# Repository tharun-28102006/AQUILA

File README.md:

# FPGA-Based Environment-Adaptive Sonar Transmitter for AUVs

**This project presents an engineering prototype for environment-adaptive sonar transmission using an FPGA.** It contains Python reference models, SystemVerilog RTL and testbenches, an analog transmitter design, a KiCad PCB layout, and a CadQuery-generated mechanical payload model. It is not a completed or field-qualified sonar product.

The repository mixes runnable models and design artifacts. Physical performance, underwater operation, and hardware integration remain to be demonstrated.

**Prototype capabilities:** 81-state table-based profile selection, three waveform modes, ping-boundary profile control, Python/RTL simulation, and companion analog, PCB, and mechanical design artifacts.

## Quick Start

1. Clone and install the Python dependencies:

   ```powershell
   git clone https://github.com/tharun-28102006/AQUILA.git
   cd AQUILA
   python -m venv .venv
   .\.venv\Scripts\Activate.ps1
   python -m pip install --upgrade pip
   python -m pip install -r requirements.txt
   ```

   On Linux/macOS, use `python3 -m venv .venv` and `source .venv/bin/activate`.
2. Run `python python_model/system_simulation.py`. Plots and summary CSVs are written to `python_model/results/`.
3. Install Icarus Verilog and run the [RTL system test](#running-the-systemverilog-rtl-simulation). It writes `build/aquila_5msps.vcd`.
4. Browse the [simulation results](#simulation-results), [KiCad board](Aquila_pcb/AQUILA_TX_PCB_FIXED.kicad_pcb), [LTspice design](AQUILA_LTSPICE/), and [mechanical drawing](aquila-freecad/AQUILA_drawing.svg).

## System Architecture

```mermaid
flowchart TD
    ENV[Environmental inputs<br/>temperature, salinity, turbidity, range/depth] --> CLS[LOW / MEDIUM / HIGH classification]
    CLS --> ENC[4 x 2-bit state encoding<br/>8-bit address]
    ENC --> LUT[81-state adaptive LUT]
    LUT --> PROF[Frequency, bandwidth, pulse duration,<br/>amplitude, waveform mode]
    PROF --> LATCH[Ping profile latch<br/>update at ping boundary]
    LATCH --> WAVE{Waveform engine}
    WAVE --> LFM[LFM chirp]
    WAVE --> GEO[Geometric sweep]
    WAVE --> PHASE[Phase-coded pulse]
    LFM --> WIN[Digital windowing]
    GEO --> WIN
    PHASE --> WIN
    WIN --> DAC[DAC interface]
    DAC --> FILTER[Analog filter]
    FILTER --> DRIVER[Output driver]
    DRIVER --> OUT[Analog output / future transducer integration]
```

This is the intended signal path represented across models and designs. Physical sensor acquisition, sustained DAC streaming, analog measurements, and transducer integration are not established by these artifacts.

### Simulation Preview

This checked-in plot is a 4 ms, 300 kHz-center LFM example from the Python model, not a measured hardware waveform. Detailed [waveforms, FFTs, spectrograms, and provenance](#simulation-results) follow below.

## Project Overview

The proposed system selects a sonar pulse profile from four environmental inputs rather than using a single fixed profile. Temperature, salinity, turbidity, and AUV-to-seabed range/depth are classified into three discrete states. The selected profile is held stable during a ping and may be replaced at the next ping boundary.

### Problem and Proposed Solution

Water conditions and operating range can change during an AUV mission. The prototype investigates deterministic profile selection and FPGA waveform generation as a reconfigurable transmitter architecture. It encodes classified inputs, looks up a precomputed profile, validates it, and latches it for the ping. The lookup avoids computing a new profile through complex runtime propagation arithmetic. Thresholds and profile policy are assumptions, not experimentally calibrated environmental or propagation data.

## How the System Works

1. Python or RTL receives numeric environmental inputs. Physical sensors and acquisition electronics are not demonstrated here.
2. The classifier maps each input to LOW, MEDIUM, or HIGH.
3. The state encoder concatenates four 2-bit states into an 8-bit LUT address.
4. The LUT supplies center frequency, bandwidth, pulse duration, amplitude, and waveform mode.
5. A safety validator checks the requested profile. The ping-profile latch captures the first valid profile and updates it only after `ping_done`.
6. The selected waveform engine generates samples. The digital path includes windowing and a DAC sample interface.
7. Python behavioral analog models and a separate LTspice design represent the filter/output chain. Physical output and acoustic stages require future validation.

### Environmental-State Classification

These are prototype thresholds, not sensor calibration specifications. Salinity and turbidity units are not defined in the model documentation.

| Input | LOW | MEDIUM | HIGH |
|---|---|---|---|
| Temperature | below 20 C | 20-30 C, inclusive | above 30 C |
| Salinity | below 300 | 300-600, inclusive | above 600 |
| Turbidity | below 20 | 20-100, inclusive | above 100 |
| Range/depth | below 1 m | 1-3 m, inclusive | above 3 m |

Python code: [`classifier.py`](python_model/classifier.py), [`environment.py`](python_model/environment.py), [`config.py`](python_model/config.py). RTL logic: [`sensor_classifier.sv`](rtl/sensor_classifier.sv). LOW, MEDIUM, and HIGH encode as `00`, `01`, and `10`; `11` is unused.

### 81-State Adaptive LUT

There are four inputs, each with three valid classes, so there are 3 x 3 x 3 x 3 = 81 valid combinations. Each class uses 2 bits; temperature, salinity, turbidity, and range/depth are concatenated in that order to form the 8-bit address. The other address patterns are not valid classifier outputs.

[`python_model/adaptive_lut.py`](python_model/adaptive_lut.py) builds and checks the reference table. RTL/Python generated tables are [`rtl/adaptive_lut.sv`](rtl/adaptive_lut.sv) and [`python_model/adaptive_lut.sv`](python_model/adaptive_lut.sv); reference data is [`python_model/adaptive_lut_reference.csv`](python_model/adaptive_lut_reference.csv). The current policy starts from a range-state profile, adjusts frequency for temperature/salinity and bandwidth for turbidity, then checks configured limits. It is a deterministic prototype policy, not a propagation-trained or experimentally calibrated LUT.

The main Python simulation selects these demonstration profiles:

| Case | Address | Center frequency | Sweep | Duration | Amplitude control | Mode |
|---|---:|---:|---:|---:|---:|---|
| Geometric | `0x50` | 400 kHz | 360-440 kHz | 2 ms | 600/1000 | Geometric |
| LFM | `0x51` | 300 kHz | 260-340 kHz | 4 ms | 800/1000 | LFM |
| Phase-coded | `0x52` | 180 kHz | 150-210 kHz | 8 ms | 1000/1000 | Phase-coded |

Amplitude is a model control on a 0-1000 scale, not a physical DAC voltage.

### Waveform Generation

The active Python system waveform builder is `generate_waveform()` in [`python_model/system_simulation.py`](python_model/system_simulation.py). The standalone LFM helper is [`python_model/waveform_lfm.py`](python_model/waveform_lfm.py). RTL mode dispatch is in [`rtl/aquila_waveform_top.sv`](rtl/aquila_waveform_top.sv) and [`rtl/mode_selector.sv`](rtl/mode_selector.sv).

#### LFM Chirp

The Python system model increments instantaneous frequency from the profile sweep start toward its end over the pulse, then applies a Hann window for analysis. RTL uses [`rtl/lfm_waveform_generator.sv`](rtl/lfm_waveform_generator.sv), [`rtl/lfm_dds.sv`](rtl/lfm_dds.sv), and the sine LUT. These are generated electrical samples, not acoustic transmission.

#### Geometric Frequency Sweep

The Python system model uses geometrically spaced instantaneous frequencies (`numpy.geomspace`). RTL uses [`rtl/geometric_waveform_engine.sv`](rtl/geometric_waveform_engine.sv), selected through the mode selector. Its frequency progression is not linear like an LFM chirp.

#### Phase-Coded Pulse

The Python model applies discrete phase reversals to a carrier. RTL uses [`rtl/phase_coded_waveform_engine.sv`](rtl/phase_coded_waveform_engine.sv) and [`rtl/phase_code_lut.sv`](rtl/phase_code_lut.sv). The separate LTspice stimulus documents its own seven-chip illustrative sequence; do not assume the implementations are identical or that they implement a named Barker code.

### Ping-Boundary Parameter Control

[`rtl/ping_profile_latch.sv`](rtl/ping_profile_latch.sv) captures the first valid profile, then holds frequency, bandwidth, duration, amplitude, and mode until `ping_done`. The system test changes requested environmental inputs during a ping and checks that the active mode changes at the boundary. Python includes a corresponding assertion in `validate_ping_boundary()`. Neither test establishes physical sensor-to-DAC operation.

## Digital Simulation

The main Python entry point is [`python_model/system_simulation.py`](python_model/system_simulation.py). It checks the demonstration environment/address, all 81 LUT profiles, frequency limits, waveform/window generation, behavioral DAC/filter/output calculations, FFT/spectrogram analysis, ping-boundary behavior, and estimated DAC-interface rates.

The main SystemVerilog integration test is [`rtl/tb_aquila_system_5msps.sv`](rtl/tb_aquila_system_5msps.sv), with top-level system wiring in [`rtl/aquila_system_top.sv`](rtl/aquila_system_top.sv). Other benches cover LUT, classifier, waveform, timing, windowing, SPI, and stream-engine blocks. Some captures are standalone or legacy-rate experiments; the 5 MSPS system test is the documented current integration bench.

## Simulation Results

The following checked-in PNGs are Python reference/system-model outputs unless otherwise stated. They are generated waveforms and numerical analyses, not oscilloscope, hydrophone, or native LTspice measurements. Per-case metrics are in [`python_model/results/system_summary.csv`](python_model/results/system_summary.csv).

### LFM Waveform

This is the windowed 4 ms LFM example at LUT address `0x51` (300 kHz center, 80 kHz bandwidth) in the 5 MSPS Python model. It shows the modeled pulse envelope and sample waveform, not a measured DAC output. See [CSV metrics](python_model/results/system_summary.csv) and [generator](python_model/system_simulation.py).

### Geometric Sweep

| Time-domain output | Time-frequency view |
|---|---|
|  |  |

This is the 2 ms, 360-440 kHz example at address `0x50`. The spectrogram shows the modeled frequency progression during the pulse.

### Phase-Coded Pulse

| Time-domain output | FFT |
|---|---|
|  |  |

This is the 8 ms phase-coded example at address `0x52`, with a 180 kHz carrier profile and 60 kHz profile bandwidth. The FFT is computed from generated, windowed samples, not measured acoustic output.

### LFM Spectrum and Spectrogram

| FFT | Spectrogram |
|---|---|
|  |  |

The FFT shows frequency-domain content from the modeled pulse; the spectrogram shows frequency change over time. Both are regenerated by the Python system simulation.

### LUT Selection and Ping Update

The profile table above comes from the checked-in [`system_summary.csv`](python_model/results/system_summary.csv), which records each demonstration case's states, address, sweep, duration, mode, and modeled output metrics. The [5 MSPS RTL VCD](aquila_5msps.vcd) and [testbench](rtl/tb_aquila_system_5msps.sv) expose `lut_address`, `requested_fc`, `requested_mode`, `active_fc`, `active_mode`, `active_valid`, `profile_valid`, `ping_done`, `sample_enable`, `waveform_sample`, and `dac_sample`. The testbench reports initial/boundary profiles and asserts that active mode does not change before `ping_done`; it does not create a dedicated profile-transition plot.

### Analog Numerical Results

This response plot comes from the independent Python/SciPy analysis, not a native LTspice run. See its [validation summary](AQUILA_LTSPICE/results/validation_summary.json) and [CSV data](AQUILA_LTSPICE/results/ac_response/filter_response.csv) for provenance and values.

Other checked-in CSV captures, VCDs, FFTs, and spectrograms are under [`rtl/`](rtl/) and [`python_model/results/`](python_model/results/). `rtl/` includes standalone and legacy-rate artifacts; do not assume every capture came from the main system test.

## Analog Signal Chain

The repository contains two different analog representations:

- [`python_model/analog_validation.py`](python_model/analog_validation.py) implements a behavioral DAC quantizer, filter, and output/load calculations. Model values and power results are assumptions/estimates, not physical measurements.
- [`AQUILA_LTSPICE/`](AQUILA_LTSPICE/) contains schematics/models for a DAC equivalent, OPA2835 buffer, two Sallen-Key filter sections, OPA2684 current-feedback output-driver equivalent, and 50-ohm load. See its README and engineering report for model provenance and limitations.

The PCB design file places an AD3541R footprint, level translators, OPA2835 buffer/filter stages, OPA2684 driver, regulator, GPIO header, external-power terminal, SMA output, and test points. These related designs are not proof of an assembled electrical implementation.

## LTspice Design

Open [`AQUILA_LTSPICE/AQUILA_TX_ANALOG.asc`](AQUILA_LTSPICE/AQUILA_TX_ANALOG.asc) for the main schematic or [`AQUILA_LTSPICE/AQUILA_FILTER_DETAIL.asc`](AQUILA_LTSPICE/AQUILA_FILTER_DETAIL.asc) for the standalone filter. The equivalent main deck is [`AQUILA_LTSPICE/AQUILA_TX_ANALOG.cir`](AQUILA_LTSPICE/AQUILA_TX_ANALOG.cir). Keep local symbols/includes/models together. Full controls and test benches are in [`AQUILA_LTSPICE/README_AQUILA_LTSPICE.md`](AQUILA_LTSPICE/README_AQUILA_LTSPICE.md).

### Native LTspice Status

Native LTspice and alternate SPICE execution were **not performed** for the checked-in numerical results. The plots and CSVs are from an independent Python/SciPy linearized numerical method; the script does not run the SPICE decks or TI macromodel. Native schematic parsing, convergence, and vendor-model compatibility remain unverified. Do not cite these artifacts as native LTspice measurements.

### Running the Numerical Analog Validation

This runs the Python/SciPy validator, not LTspice. From the repository root:

```powershell
python -m pip install -r .\AQUILA_LTSPICE\scripts\requirements.txt
python .\AQUILA_LTSPICE\scripts\validate_numerically.py
```

It writes plots, CSVs, and JSON under `AQUILA_LTSPICE/results/`. [`AQUILA_LTSPICE/scripts/requirements.txt`](AQUILA_LTSPICE/scripts/requirements.txt) pins this tool's dependencies. [`build_project.py`](AQUILA_LTSPICE/scripts/build_project.py) regenerates design files from a manifest and can overwrite manual edits. To inspect the design, install LTspice separately and open the `.asc` file with its sibling symbols, includes, and models in place.

## PCB Design

The board source is [`Aquila_pcb/AQUILA_TX_PCB_FIXED.kicad_pcb`](Aquila_pcb/AQUILA_TX_PCB_FIXED.kicad_pcb), a KiCad 10-format board. There is no matching `.kicad_sch`, BOM, exported fabrication package, PCB render, or included DRC report. Board dimensions are not documented separately in the reports.

The placed design identifies an AD3541R DAC footprint, SN74AXC4T774 level translators, OPA2835 buffer/filter stages, OPA2684 output driver, AP2112K 1.8 V regulator, DE10-Lite GPIO header, external-power terminal, SMA output, and labeled test points/nets. The apparent signal path from the component/net labels is DE10-Lite GPIO header -> level translators -> DAC -> OPA2835 buffer -> two filter sections -> OPA2684 output driver -> SMA/output. This is an interpretation of the board file, not a verified signal-chain test; there is no matching schematic. These are design-file details, not evidence of DRC clearance, fabrication, assembly, or testing. Verify schematic correspondence, footprints, routing, clearances, and ratings before manufacturing. No KiCad CLI/rendering tool was available, so no board image or DRC result is claimed here.

## Mechanical CAD / Payload

The mechanical package describes a transmitter enclosure and payload layout, not a receiver/hydrophone assembly. Its nominal envelope is approximately 330 mm long x 138 mm wide x 129 mm high; the shell is 300 mm long, 110 mm outside diameter, and 102 mm inside diameter. The drawing is a general arrangement, not a released fabrication drawing.

- [Assembled named-part STEP](aquila-freecad/AQUILA_assembly.step)
- [Exploded STEP presentation model](aquila-freecad/AQUILA_exploded.step); exploded positions are not assembly positions
- [Individual STEP and STL parts](aquila-freecad/parts/)
- [Printable-parts ZIP](aquila-freecad/AQUILA_printable_parts.zip), containing 11 custom printable parts
- [Parametric CadQuery source](aquila-freecad/source/aquila.py)
- [Build notes](aquila-freecad/BUILD_NOTES.md) and [validation metadata](aquila-freecad/validation.json)

No native FreeCAD `.FCStd` file is included; the editable master is the CadQuery Python source. Recorded CAD checks cover B-rep validity and selected nominal fit/STEP round trips, not comprehensive tolerance, pressure, seal, thermal, fatigue, or certification analyses. The housing is **not pressure-rated or certified waterproof**. Some board/connector envelopes are placeholders pending measurement against actual parts.

## Complete Development Flow

```mermaid
flowchart LR
    A[Environmental model] --> B[State classifier and encoder]
    B --> C[Adaptive LUT]
    C --> D[Profile and ping latch]
    D --> E[SystemVerilog waveform RTL]
    E --> F[Python and RTL simulations]
    F --> G[Analog design and numerical analysis]
    G --> H[KiCad PCB design]
    H --> I[Mechanical integration model]
    I -. future .-> J[Bench electrical and thermal validation]
    J -. future .-> K[Water, tank, transducer testing]
    K -. future .-> L[AUV integration and field evaluation]
```

The code, simulations, analog/PCB designs, and CAD package are present. Dotted stages are future validation, not completed milestones.

## Repository Structure

| Path | Contents |
|---|---|
| [`python_model/`](python_model/) | Python models, simulations, LUT tools, analog/transducer studies, validators, results. |
| [`python_model/results/`](python_model/results/) | System summary and analog-response CSVs, waveform/FFT/spectrogram PNGs. |
| [`rtl/`](rtl/) | SystemVerilog modules/testbenches, capture-analysis scripts, CSVs, plots, and historical simulation artifacts. |
| [`Aquila_pcb/`](Aquila_pcb/) | KiCad PCB layout only; no matching schematic/BOM. |
| [`AQUILA_LTSPICE/`](AQUILA_LTSPICE/) | Schematics, decks, includes, symbols/models, numerical scripts and result files. |
| [`aquila-freecad/`](aquila-freecad/) | STEP/STL, CadQuery source, drawing, parameters, build notes, manifest, checksums, validation. |
| [`AQUILA_AUDIT_REPORT.md`](AQUILA_AUDIT_REPORT.md) | Architecture audit, interface rates, and outstanding hardware work. |
| [`requirements.txt`](requirements.txt) | Python dependencies for the main model/analysis scripts. |

The transducer-aware scripts and related files in `python_model/` are historical study artifacts, not the active final system path. Existing VCD, CSV, and PNG files are reference results; compiled simulator executables are not source.

## Requirements and Tools

| Area | Technology |
|---|---|
| FPGA target context | Intel MAX 10 / DE10-Lite appears in project interfaces/CAD notes; physical timing closure is not established. |
| HDL / RTL simulation | SystemVerilog; Icarus Verilog (`iverilog`, `vvp`); GTKWave optional for viewing VCD. |
| Python model | Python 3, NumPy, SciPy, Matplotlib; pandas is used by capture-analysis utilities. |
| Analog design | LTspice-compatible `.asc`/`.cir` sources and local models; native execution unverified. |
| Analog numerical analysis | Python/NumPy/SciPy/Matplotlib; pinned requirements in `AQUILA_LTSPICE/scripts/requirements.txt`. |
| PCB | KiCad 10-format board source. |
| Mechanical | CadQuery 2.5.2 source; STEP/STL viewable in FreeCAD or another compatible CAD tool. |
| Version control | Git / GitHub |

## Installation

### Python

Windows PowerShell:

```powershell
python -m venv .venv
.\.venv\Scripts\Activate.ps1
python -m pip install --upgrade pip
python -m pip install -r requirements.txt
```

Linux or macOS:

```bash
python3 -m venv .venv
source .venv/bin/activate
python -m pip install --upgrade pip
python -m pip install -r requirements.txt
```

If activation is blocked, invoke `.\.venv\Scripts\python.exe -m pip install -r requirements.txt` and use `.\.venv\Scripts\python.exe` to run the model.

### RTL Simulator

Install Icarus Verilog with SystemVerilog support and put `iverilog` and `vvp` on `PATH`. Install GTKWave separately if you want a VCD GUI. The compile/run commands below were verified with Icarus Verilog 12.0; this version prints some non-fatal `constant selects in always_*` warnings for the current RTL.

## Running the Python Model

From the repository root with the environment active:

```powershell
python python_model/system_simulation.py
```

This prints PASS checks and creates/updates `system_summary.csv`, `analog_response.csv`, and available mode-specific time, FFT, and spectrogram plots in `python_model/results/`. Analog-chain and power values are modeled estimates, not physical measurements.

Other scripts include [`waveform_lfm.py`](python_model/waveform_lfm.py), [`adaptive_lut.py`](python_model/adaptive_lut.py), [`analog_validation.py`](python_model/analog_validation.py), and [`fft_analysis.py`](python_model/fft_analysis.py). Some scripts are standalone or historical; inspect their assumptions before treating output as part of the main system validation.

## Running the SystemVerilog RTL Simulation

The integration test is `tb_aquila_system_5msps` in [`rtl/tb_aquila_system_5msps.sv`](rtl/tb_aquila_system_5msps.sv). It checks profile safety, ping-boundary changes, and sample-enable timing. Its 50 MHz clock and 5 MSPS internal sample-enable target correspond to 200 ns between events.

Windows PowerShell, from the repository root:

```powershell
New-Item -ItemType Directory -Force .\build | Out-Null
$rtl = Get-ChildItem .\rtl -Filter *.sv |
    ForEach-Object { $_.FullName }

iverilog -g2012 `
    -s tb_aquila_system_5msps `
    -o .\build\aquila_5msps.vvp `
    $rtl

if ($LASTEXITCODE -eq 0) {
    Push-Location .\build
    try {
        vvp .\aquila_5msps.vvp
    }
    finally {
        Pop-Location
    }
}
```

Linux/macOS, from the repository root:

```bash
mkdir -p build
iverilog -g2012 \
    -s tb_aquila_system_5msps \
    -o build/aquila_5msps.vvp \
    rtl/*.sv

(cd build && vvp ./aquila_5msps.vvp)
```

Expected success line: `PASS: Aquila 5-MSPS system-level RTL simulation`. The VCD is written to `build/aquila_5msps.vcd`, and `build/` is Git-ignored. The existing root `aquila_5msps.vcd` is a checked-in reference capture and is not overwritten by these commands.

## Viewing Waveform Results

Open the generated VCD from the repository root:

```powershell
gtkwave .\build\aquila_5msps.vcd
```

On Linux/macOS, use `gtkwave build/aquila_5msps.vcd`. Useful testbench signals are `temperature_state`, `salinity_state`, `turbidity_state`, `range_state`, `lut_address`, `requested_fc`, `requested_mode`, `active_fc`, `active_mode`, `active_valid`, `profile_valid`, `ping_done`, `sample_enable`, `waveform_sample`, and `dac_sample`. They are declared in the testbench and present in the VCD header. GTKWave is optional for running the test.

## Viewing the KiCad PCB

Open [`Aquila_pcb/AQUILA_TX_PCB_FIXED.kicad_pcb`](Aquila_pcb/AQUILA_TX_PCB_FIXED.kicad_pcb) in KiCad. Only the board file is present; there is no companion schematic, BOM, render, fabrication output, or DRC report. Verify the design and manufacturing constraints before use.

## Viewing LTspice and Running Numerical Validation

Open [`AQUILA_LTSPICE/AQUILA_TX_ANALOG.asc`](AQUILA_LTSPICE/AQUILA_TX_ANALOG.asc) in LTspice with sibling symbols, includes, and models in place. The standalone filter schematic is [`AQUILA_LTSPICE/AQUILA_FILTER_DETAIL.asc`](AQUILA_LTSPICE/AQUILA_FILTER_DETAIL.asc). See the [LTspice project guide](AQUILA_LTSPICE/README_AQUILA_LTSPICE.md) for test decks, control values, traces, and model provenance.

The checked-in result plots are from independent Python/SciPy linearized analysis, **not native LTspice**. Native LTspice and alternate SPICE execution were not performed for these results; native parsing, convergence, and vendor-model compatibility remain unverified.

To run the numerical analog validator from the repository root (this does not run LTspice):

```powershell
python -m pip install -r .\AQUILA_LTSPICE\scripts\requirements.txt
python .\AQUILA_LTSPICE\scripts\validate_numerically.py
```

It writes plots, CSVs, and a JSON summary under `AQUILA_LTSPICE/results/`. [`AQUILA_LTSPICE/scripts/requirements.txt`](AQUILA_LTSPICE/scripts/requirements.txt) pins the analysis dependencies. [`build_project.py`](AQUILA_LTSPICE/scripts/build_project.py) regenerates design files from a manifest and can overwrite manual edits.

## Mechanical CAD / Payload

This is a transmitter enclosure/payload layout, not a receiver/hydrophone assembly. The nominal envelope is about 330 x 138 x 129 mm; the shell is 300 mm long, 110 mm outside diameter, and 102 mm inside diameter. The SVG is a general-arrangement drawing, not a fabrication release.

- [Assembly STEP](aquila-freecad/AQUILA_assembly.step)
- [Exploded STEP](aquila-freecad/AQUILA_exploded.step) (presentation positions, not assembly positions)
- [Individual STEP/STL parts](aquila-freecad/parts/)
- [Printable-parts ZIP](aquila-freecad/AQUILA_printable_parts.zip) (11 custom printable parts)
- [Parametric CadQuery source](aquila-freecad/source/aquila.py)
- [Build notes](aquila-freecad/BUILD_NOTES.md) and [validation metadata](aquila-freecad/validation.json)

No native FreeCAD `.FCStd` file is included; the editable master is the CadQuery source. Recorded checks cover B-rep validity and selected nominal fit/STEP round trips, not comprehensive tolerance, pressure, seal, thermal, fatigue, or certification analyses. The enclosure is **not pressure-rated or certified waterproof**. Some board/connector envelopes are placeholders pending measurement against actual hardware.

## Complete Development Flow

```mermaid
flowchart LR
    A[Environmental model] --> B[State classifier and encoder]
    B --> C[Adaptive LUT]
    C --> D[Profile and ping latch]
    D --> E[SystemVerilog waveform RTL]
    E --> F[Python and RTL simulations]
    F --> G[Analog design and numerical analysis]
    G --> H[KiCad PCB design]
    H --> I[Mechanical integration model]
    I -. future .-> J[Bench electrical and thermal validation]
    J -. future .-> K[Water, tank, transducer testing]
    K -. future .-> L[AUV integration and field evaluation]
```

Code, simulations, analog/PCB designs, and CAD are present. Dotted stages are future validation, not completed milestones.

## Repository Structure

| Path | Contents |
|---|---|
| [`python_model/`](python_model/) | Python models, simulation, LUT tools, analog/transducer studies, validators, results. |
| [`python_model/results/`](python_model/results/) | System summary/analog CSVs and mode-specific time, FFT, spectrogram PNGs. |
| [`rtl/`](rtl/) | SystemVerilog modules/testbenches, capture-analysis scripts, CSVs, plots, historical artifacts. |
| [`Aquila_pcb/`](Aquila_pcb/) | KiCad PCB layout; no matching schematic/BOM. |
| [`AQUILA_LTSPICE/`](AQUILA_LTSPICE/) | Schematics, decks, includes, symbols/models, numerical scripts/results. |
| [`aquila-freecad/`](aquila-freecad/) | STEP/STL exports, CadQuery source, drawing, parameters, notes, manifest/checksums/validation. |
| [`AQUILA_AUDIT_REPORT.md`](AQUILA_AUDIT_REPORT.md) | Architecture audit, interface rates, open hardware work. |
| [`requirements.txt`](requirements.txt) | Main Python dependencies. |

Transducer-aware Python files are historical study artifacts identified by the audit, not the active final system path. Existing VCD/CSV/PNG files are reference results; compiled simulator executables are not source.

## Tools and Technologies

| Area | Technology |
|---|---|
| FPGA target context | Intel MAX 10 / DE10-Lite references; physical timing closure not established. |
| HDL / RTL simulation | SystemVerilog; Icarus Verilog; GTKWave optional. |
| Python modeling | Python 3, NumPy, SciPy, Matplotlib; pandas for capture-analysis utilities. |
| Analog design | LTspice-compatible schematics/decks; native execution unverified. |
| Numerical analog analysis | Python/NumPy/SciPy/Matplotlib; separate pinned requirements file. |
| PCB | KiCad 10-format board. |
| Mechanical | CadQuery 2.5.2; STEP/STL compatible with FreeCAD and other CAD tools. |
| Version control | Git / GitHub |

## Benefits and Potential Applications

The architecture provides deterministic LUT-based profile selection, selectable waveform modes, a profile held constant within a ping, and separate digital, analog, PCB, and mechanical artifacts. These are design characteristics, not experimentally demonstrated benefits; power, reliability, adaptation quality, and acoustic performance are not proven on deployed hardware.

Potential research contexts include seabed mapping, subsea infrastructure inspection, underwater surveillance studies, marine research, fisheries/ecosystem studies, and AUV prototype development. These are possible applications, not validated field deployments.

## Validation Status

| Area | Evidence/status |
|---|---|
| Python classifier, state encoding, LUT, waveforms, behavioral analog model | Implemented; system validation runs and reports PASS for programmed checks. |
| SystemVerilog modules and testbenches | Present; main Icarus integration test run successfully during this documentation update. |
| Internal 5 MSPS sample-enable timing | Simulated at 50 MHz with 200 ns intervals. |
| Sustained 5 MSPS DAC stream | Not achieved by the audited interfaces. |
| LTspice source | Schematics, decks, symbols, and models present. |
| Analog numerical plots/CSV | Independent Python/SciPy linearized results; not native LTspice measurements. |
| Native LTspice/alternate SPICE execution | Not performed for the checked-in numerical results. |
| KiCad PCB | Layout source present; no DRC report, fabrication, assembly, or board test evidence. |
| Mechanical CAD | STEP/STL and CadQuery source present; B-rep and selected nominal fit/round-trip checks recorded. |
| Waterproof/pressure validation | Not performed; no rating/certification. |
| Hydrophone/tank/transducer testing | Not present. |
| AUV integration/field deployment | Not established. |

### Important Interface Throughput Note

The system-level RTL test exercises an internal 5 MSPS sample-enable event from a 50 MHz clock. This validates digital timing in simulation, not sustained DAC output. The audit estimates about 416.7 kSPS for the single-lane 24-bit SPI path at 10 MHz and about 520.8 kSPS for the dual-SPI/DDR-style path at approximately 8.333 MHz and 16 serial-clock cycles per sample. Neither audited interface reaches 5 MSPS. Sustained DAC delivery and physical interface timing remain open integration/measurement tasks.

## Known Limitations

- Sensor thresholds, units (except temperature/range conventions), and LUT policy are prototype assumptions requiring calibration and experimental review.
- The 100-500 kHz region is an electrical profile/safety region, not demonstrated acoustic bandwidth, sonar range, or imaging performance.
- Python analog stages, DAC behavior, component values, load, and power are models/estimates, not hardware characterization.
- Native LTspice decks were not executed for the checked-in results; Python/SciPy analysis does not run the SPICE decks or vendor model.
- The PCB lacks a companion schematic/BOM and fabrication/DRC evidence. Verify electrical/mechanical correspondence before manufacturing.
- The housing is not pressure-rated or certified waterproof. Board outlines, heights, connectors, seals, fasteners, cable routing, and fits require measurement against selected hardware.
- No physical FPGA timing closure, DAC throughput measurement, oscilloscope/thermal/water test, hydrophone measurement, or AUV deployment is established.

## Future Development

1. Confirm physical sensor interfaces, calibrate thresholds, and experimentally review LUT policy.
2. Select/verify an FPGA-DAC interface for required sustained output rate and close target-hardware timing.
3. Match schematic, PCB, BOM, footprints, and electrical rules; then fabricate and bench-test.
4. Measure the analog chain, loading, thermal behavior, and power.
5. Replace CAD placeholders with measured hardware and review seals, tolerances, thermal paths, and hull interfaces.
6. Plan controlled transducer/tank work and later AUV integration only after appropriate bench validation.

## Where Should I Start?

- **New to Project:** read the [Project Overview](#project-overview), [System Architecture](#system-architecture), [How the System Works](#how-the-system-works), and [Simulation Results](#simulation-results).
- **Run the Python model:** see [requirements](requirements.txt) and [`python_model/system_simulation.py`](python_model/system_simulation.py).
- **Inspect RTL:** start with [`rtl/aquila_system_top.sv`](rtl/aquila_system_top.sv), [`rtl/aquila_top.sv`](rtl/aquila_top.sv), [`rtl/ping_profile_latch.sv`](rtl/ping_profile_latch.sv), and [`rtl/tb_aquila_system_5msps.sv`](rtl/tb_aquila_system_5msps.sv).
- **Inspect analog design:** open [`AQUILA_LTSPICE/`](AQUILA_LTSPICE/) and its project README.
- **Inspect the PCB:** open [`Aquila_pcb/AQUILA_TX_PCB_FIXED.kicad_pcb`](Aquila_pcb/AQUILA_TX_PCB_FIXED.kicad_pcb) in a compatible KiCad release.
- **Inspect mechanics:** view the [GA drawing](aquila-freecad/AQUILA_drawing.svg), [assembly STEP](aquila-freecad/AQUILA_assembly.step), or [build notes](aquila-freecad/BUILD_NOTES.md).
- **Reproduce numerical analog plots:** install `AQUILA_LTSPICE/scripts/requirements.txt` and run `python AQUILA_LTSPICE/scripts/validate_numerically.py`; results remain Python/SciPy analyses.

## Development and Contributing

There is no separate contribution guide. Keep changes scoped to the owning model/design, document assumptions, and distinguish generated/model results from measured evidence. The LTspice build script can regenerate and overwrite design files. For CAD generation, the parameter table in `aquila-freecad/source/aquila.py` is authoritative; changing exported JSON alone does not rebuild geometry. Avoid committing simulator caches and generated binaries.

## License

No repository-level `LICENSE` file is present, so project-wide reuse/redistribution terms are unspecified. The LTspice package includes a vendor model/archive with its own copyright and disclaimer; retain those notices. Contact project maintainers for permission or clarification before redistribution.

## Disclaimer

This repository contains the engineering prototype, development models, simulations, and design artifacts for the proposed sonar transmitter. It does not establish a completed sonar product, measured low-power operation, underwater acoustic performance, safe pressure housing, or AUV deployment. Independently review and validate electrical, mechanical, safety, and environmental requirements before building or testing hardware.

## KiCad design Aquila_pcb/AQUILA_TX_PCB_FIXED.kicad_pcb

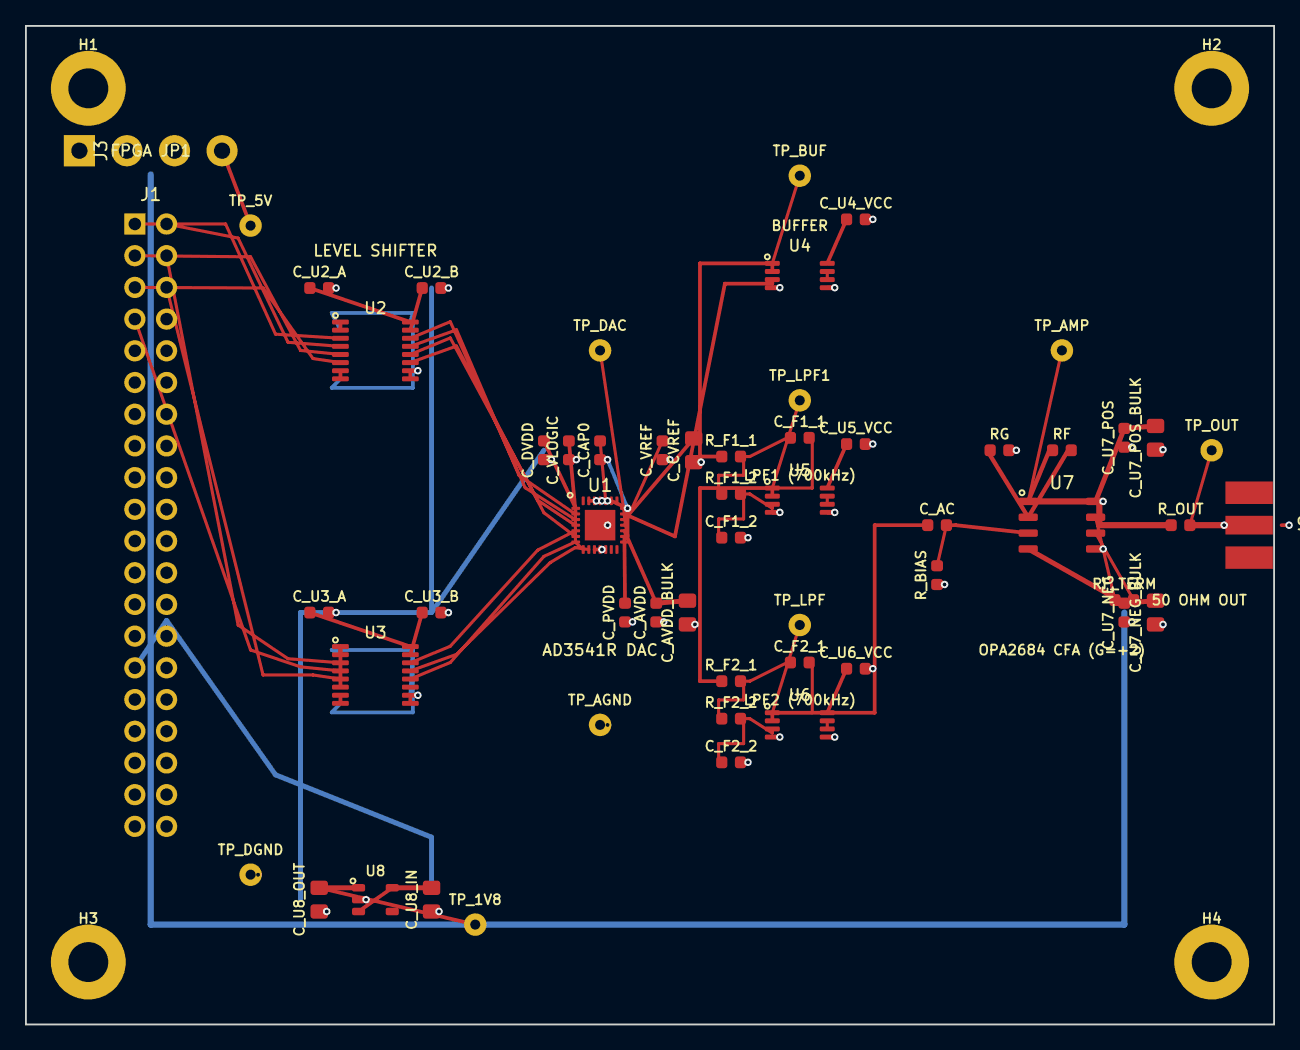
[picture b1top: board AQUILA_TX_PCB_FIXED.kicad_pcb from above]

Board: 4 copper layers, 100.0 x 80.0 mm, 60 parts (0 on the bottom side), 39 nets.

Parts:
C_AC: 100nF; C_0603_1608Metric
C_AVDD: 100nF; C_0603_1608Metric
C_AVDD_BULK: 10uF; C_0805_2012Metric
C_CAP0: 100nF; C_0603_1608Metric
C_CVREF: 4.7uF; C_0805_2012Metric
C_DVDD: 100nF; C_0603_1608Metric
C_F1_1: 390pF; C_0603_1608Metric
C_F1_2: 330pF; C_0603_1608Metric
C_F2_1: 680pF; C_0603_1608Metric
C_F2_2: 100pF; C_0603_1608Metric
C_PVDD: 100nF; C_0603_1608Metric
C_U2_A, C_U2_B, C_U3_A, C_U3_B, C_U4_VCC, C_U5_VCC, C_U6_VCC, C_U7_NEG, C_U7_POS: 100nF; C_0603_1608Metric
C_U7_NEG_BULK, C_U7_POS_BULK: 6.8uF; C_0805_2012Metric
C_U8_IN, C_U8_OUT: 1uF; C_0805_2012Metric
C_VLOGIC: 100nF; C_0603_1608Metric
C_VREF: 100nF; C_0603_1608Metric
H1, H2, H3, H4: MountingHole_3.2mm_M3_Pad_Via
J1: DE10-Lite GPIO[0]; PinHeader_2x20_P2.54mm_Vertical
J2: SMA_50R; SMA_Amphenol_132134-10_EdgeMount
J3: EXT_POWER; TerminalBlock_bornier-4_P5.08mm
RF: 402R; R_0603_1608Metric
RF_TERM: 402R; R_0603_1608Metric
RG: 402R; R_0603_1608Metric
R_BIAS: 10k; R_0603_1608Metric
R_F1_1, R_F1_2: 634R; R_0603_1608Metric
R_F2_1, R_F2_2: 866R; R_0603_1608Metric
R_OUT: 10R; R_0603_1608Metric
TP_1V8, TP_5V: TestPoint_THTPad_D1.5mm_Drill0.8mm
TP_AGND: TestPoint_THTPad_D1.5mm_Drill0.8mm
TP_AMP: TestPoint_THTPad_D1.5mm_Drill0.8mm
TP_BUF: TestPoint_THTPad_D1.5mm_Drill0.8mm
TP_DAC: TestPoint_THTPad_D1.5mm_Drill0.8mm
TP_DGND: TestPoint_THTPad_D1.5mm_Drill0.8mm
TP_LPF, TP_LPF1: TestPoint_THTPad_D1.5mm_Drill0.8mm
TP_OUT: TestPoint_THTPad_D1.5mm_Drill0.8mm
U1: AD3541RBCPZ12; LFCSP-28-1EP_4x4mm_P0.45mm_EP2.45x2.45mm
U2, U3: SN74AXC4T774; TSSOP-16_4.4x5mm_P0.65mm
U4: OPA2835_BUF; VSSOP-8_3.0x3.0mm_P0.65mm
U5: OPA2835_LPF1; VSSOP-8_3.0x3.0mm_P0.65mm
U6: OPA2835_LPF2; VSSOP-8_3.0x3.0mm_P0.65mm
U7: OPA2684; SOIC-8_3.9x4.9mm_P1.27mm
U8: AP2112K-1.8; SOT-23-5

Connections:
+1.8V: C_DVDD.1, C_U2_B.1, C_U3_B.1, C_U8_OUT.1, C_VLOGIC.1, TP_1V8.1, U1.1, U1.2, U2.15, U3.15, U8.1
+3.3V: C_U2_A.1, C_U3_A.1, C_U8_IN.1, J1.29, J3.4, U2.1, U2.2, U2.7, U2.8, U2.16, U3.7, U3.8, U3.16, U8.3, U8.5
+5V: C_AVDD.1, C_AVDD_BULK.1, C_PVDD.1, C_U4_VCC.1, C_U5_VCC.1, C_U6_VCC.1, C_U7_POS.1, C_U7_POS_BULK.1, J1.11, J3.1, TP_5V.1, U1.16, U1.17, U4.8, U5.8, U6.8, U7.8
-5V: C_U7_NEG.1, C_U7_NEG_BULK.1, J3.3, U7.4
ALERT_1V8: U1.9, U3.13
ALERT_3V3: J1.7, U3.4
AMP_IN_M: RF.2, RG.1, U7.2
AMP_IN_P: C_AC.2, R_BIAS.1, U7.3
AMP_OUT: RF.1, R_OUT.1, TP_AMP.1, U7.1
BUF_OUT: R_F1_1.1, TP_BUF.1, U4.1, U4.2
CAP0: C_CAP0.1, U1.24
CS_1V8: U1.3, U2.13
CS_3V3: J1.2, U2.4
CVREF: C_CVREF.1, U1.19
DAC_OUT: TP_DAC.1, U1.20, U1.23, U4.3
GND: C_AVDD.2, C_AVDD_BULK.2, C_CAP0.2, C_CVREF.2, C_DVDD.2, C_F1_2.2, C_F2_2.2, C_PVDD.2, C_U2_A.2, C_U2_B.2, C_U3_A.2, C_U3_B.2, C_U4_VCC.2, C_U5_VCC.2, C_U6_VCC.2, C_U7_NEG.2, C_U7_NEG_BULK.2, C_U7_POS.2, C_U7_POS_BULK.2, C_U8_IN.2, C_U8_OUT.2, C_VLOGIC.2, C_VREF.2, H1.1, H2.1, H3.1, H4.1, J1.12, J1.30, J2.2, J2.3, J2.4, J2.5, J3.2, RG.2, R_BIAS.2, TP_AGND.1, TP_DGND.1, U1.10, U1.25, U1.26, U1.27, U1.29, U2.9, U2.10, U3.1, U3.2, U3.6, U3.9, U3.10, U4.4, U4.5, U5.4, U5.5, U6.4, U6.5, U7.5, U8.2
LDAC_1V8: U1.7, U2.11
LDAC_3V3: J1.5, U2.6
LPF1_IN_P: C_F1_2.1, R_F1_2.2, U5.3
LPF1_MID: C_F1_1.1, R_F1_1.2, R_F1_2.1
LPF1_OUT: C_F1_1.2, R_F2_1.1, TP_LPF1.1, U5.1, U5.2
LPF2_IN_P: C_F2_2.1, R_F2_2.2, U6.3
LPF2_MID: C_F2_1.1, R_F2_1.2, R_F2_2.1
LPF2_OUT: C_AC.1, C_F2_1.2, TP_LPF.1, U6.1, U6.2
OUTPUT: J2.1, R_OUT.2, TP_OUT.1
RESET_1V8: U1.8, U3.12
RESET_3V3: J1.6, U3.5
SCLK_1V8: U1.4, U2.14
SCLK_3V3: J1.1, U2.3
SDI_1V8: U1.5, U2.12
SDI_3V3: J1.3, U2.5
SDO_1V8: U1.6, U3.14
SDO_3V3: J1.4, U3.3
U4_TERM: U4.6, U4.7
U5_TERM: U5.6, U5.7
U6_TERM: U6.6, U6.7
U7_OUT2: RF_TERM.1, U7.7
U7_TERM: RF_TERM.2, U7.6
VREF: C_VREF.1, U1.18
